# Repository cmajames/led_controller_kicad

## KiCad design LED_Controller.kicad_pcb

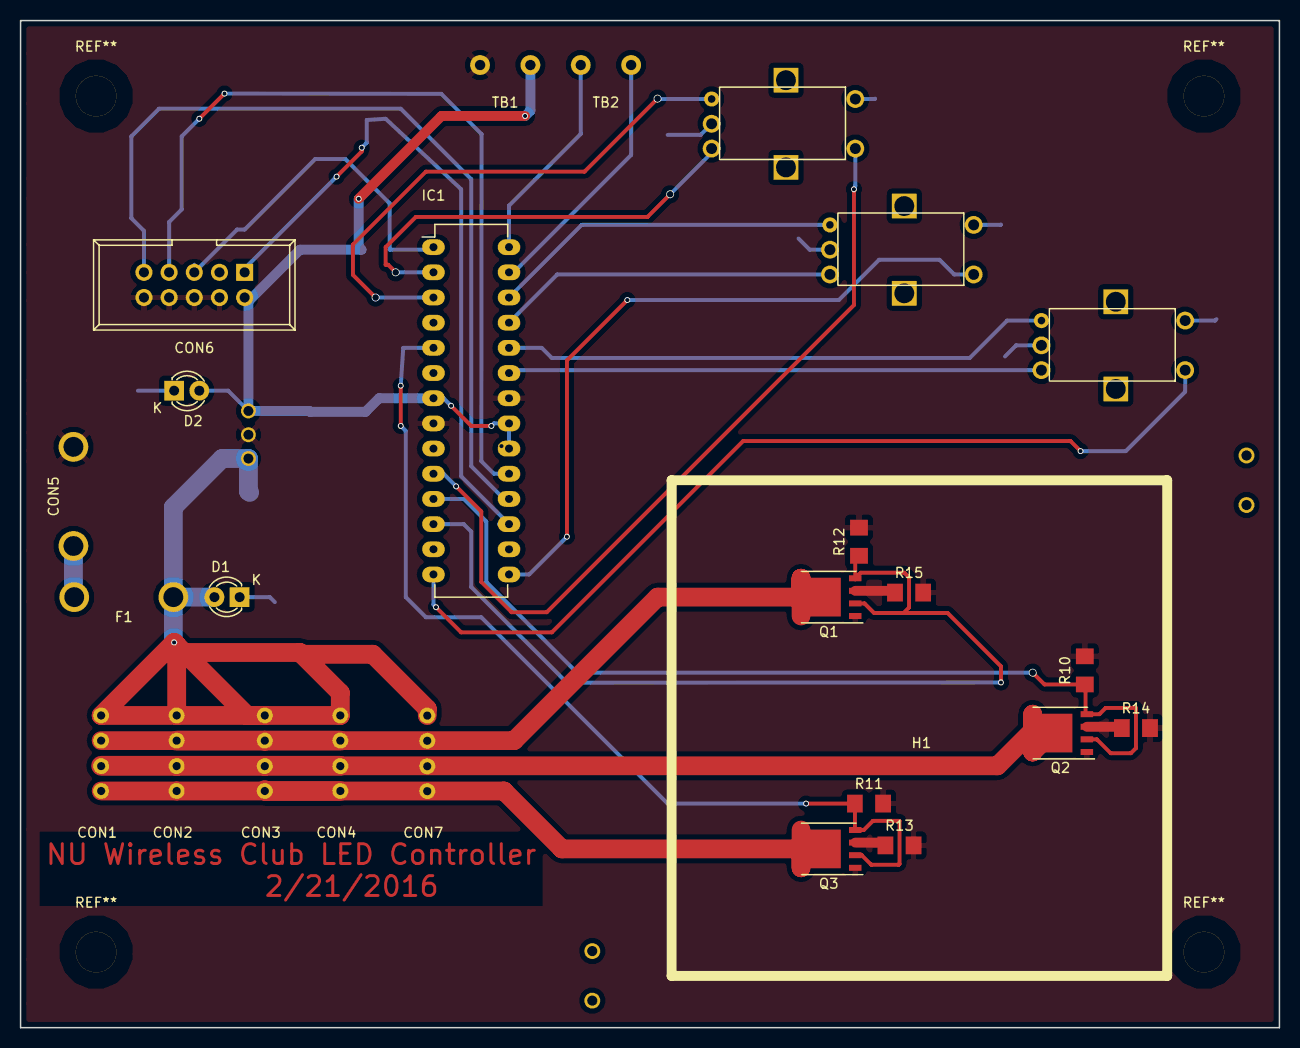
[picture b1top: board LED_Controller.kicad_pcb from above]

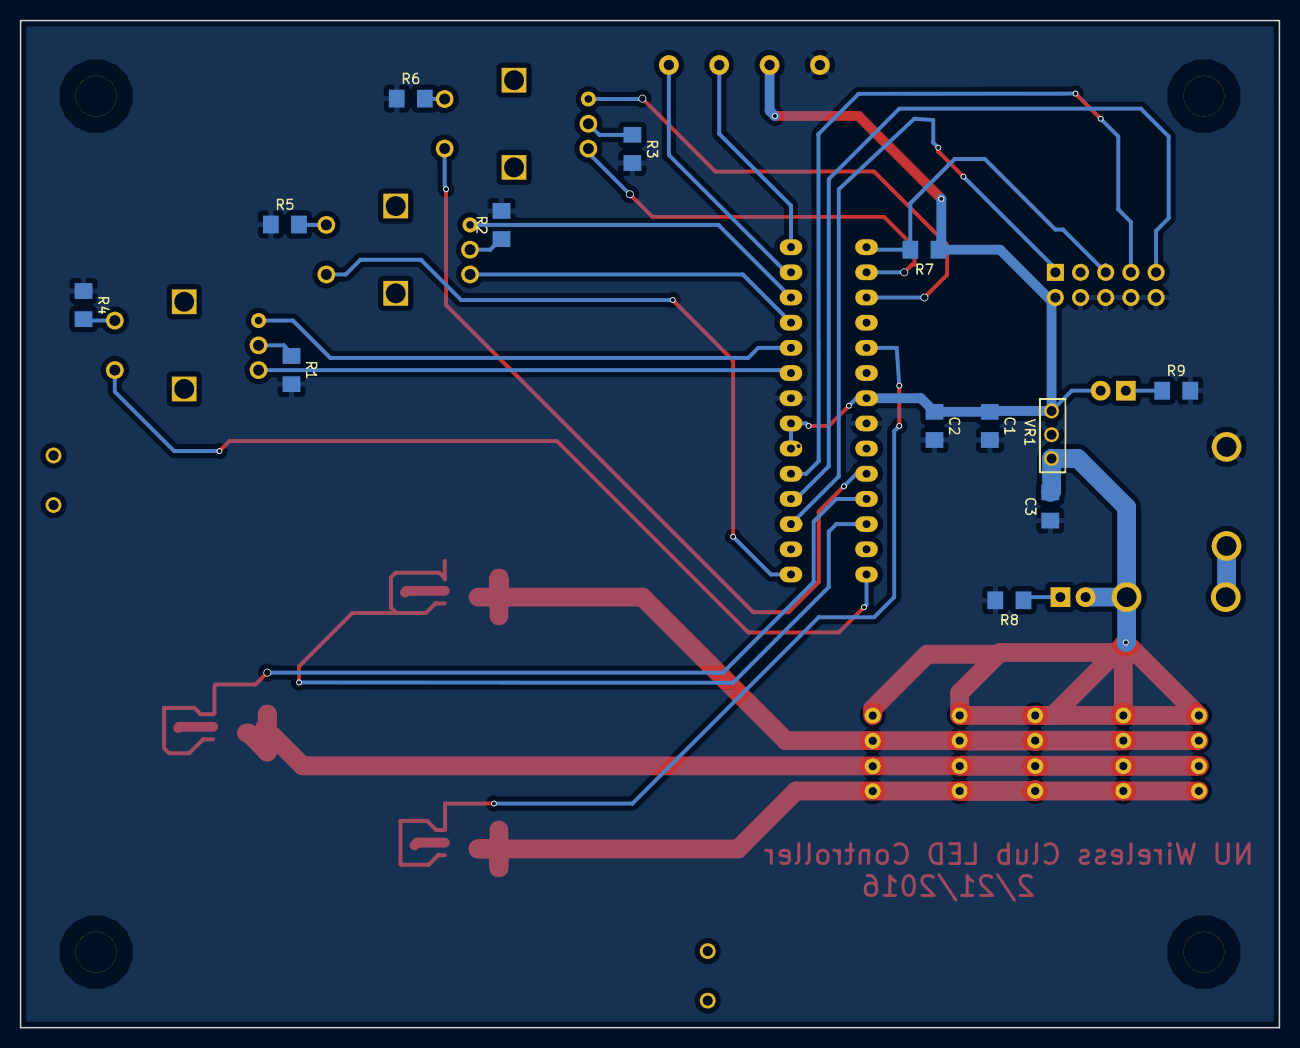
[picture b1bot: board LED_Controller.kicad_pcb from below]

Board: 2 copper layers, 127.0 x 101.6 mm, 39 parts (13 on the bottom side), 33 nets.

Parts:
C1, C3: 10uF; SMD_1206
C2: .1uF; SMD_1206
CON1, CON2, CON3, CON4, CON7: CONNECTOR; OUTPUT_HOLES
CON5: PWR_CON; 12V_PWR_HOLES
CON6: AVR-ISP-10; IDC_Header_Straight_10pins
D1, D2: LED; LED-3MM
E1, E2, E3: Rotary_Encoder; Rotary_encoder
F1: FUSE; 12V_PWR_HOLES
H1: Heatsink_50x50mm
IC1: ATMEGA328P-P; DIP-28_W7.62mm_LongPads
Q1, Q2, Q3: STS8DN3LLH5; SO-8_PowerPAK_Vishay_Single
R1, R2, R3, R4, R5, R6, R7, R10, R11, R12: 10k; SMD_1206
R8: 820; SMD_1206
R9: 499; SMD_1206
R13, R14, R15: 0; SMD_1206
TB1, TB2: Terminal_Block_2pin; Screw_Terminal
VR1: L7805CV

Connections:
+5V: C1.1, C2.1, CON6.2, D2.2, IC1.7, IC1.20, IC1.21, R7.1, TB1.1, VR1.3
+12V: C3.2, CON1.4, CON2.4, CON3.4, CON4.4, CON7.4, D1.2, F1.1, VR1.1
/BLUE_5V: IC1.12, Q1.2, Q1.4, R12.1
/BLUE_PWR: CON1.3, CON2.3, CON3.3, CON4.3, CON7.3, Q1.5
/GREEN_5V: IC1.11, Q2.2, Q2.4, R10.1
/GREEN_PWR: CON1.2, CON2.2, CON3.2, CON4.2, CON7.2, Q2.5
/MISO: CON6.9, IC1.18
/MOSI: CON6.1, IC1.17
/RED_5V: IC1.5, Q3.2, Q3.4, R11.1
/RED_PWR: CON1.1, CON2.1, CON3.1, CON4.1, CON7.1, Q3.5
/RST: CON6.5, IC1.1, R7.2
/SCK: CON6.7, IC1.19
/SCL: IC1.28, TB2.2
/SDA: IC1.27, TB2.1
GND: C1.2, C2.2, C3.1, CON5.2, CON6.4, CON6.6, CON6.8, CON6.10, IC1.8, IC1.22, Q1.1, Q1.3, Q2.1, Q2.3, Q3.1, Q3.3, R1.2, R2.2, R3.2, R4.1, R5.1, R6.1, R8.2, R9.2, R10.2, R11.2, R12.2, R13.1, R13.2, R14.1, R14.2, R15.1, R15.2, TB1.2, VR1.2
unnamed: CON5.1, F1.2
unnamed: D1.1, R8.1
unnamed: D2.1, R9.1
unnamed: E1.1, IC1.14
unnamed: E1.2, R4.2
unnamed: E1.3, R1.1
unnamed: E1.4, IC1.23
unnamed: E1.5, IC1.24
unnamed: E2.1, IC1.15
unnamed: E2.2, R5.2
unnamed: E2.3, R2.1
unnamed: E2.4, IC1.25
unnamed: E2.5, IC1.26
unnamed: E3.1, IC1.10
unnamed: E3.2, R6.2
unnamed: E3.3, R3.1
unnamed: E3.4, IC1.2
unnamed: E3.5, IC1.3

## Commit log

2016-02-14 Added kicad files
    Added schematic, PCB, and library files
2016-02-15 Minor Changes
    Added a pull-up resistor to RST, to ensure chip is not reset during
    normal use. Some minor changes to the track layout.
2016-02-19 Changed to Common Anode, new status LEDs
    Updated schematic to reflect common anode LED strip, instead of common
    cathode.
    Added indicator LEDs to 12V and 5V power supply.
    Other minor routing changes. Still need to update footprint to make
    rotary encoder pins larger and probably change the Atmega footprint to
    the correct size.
2016-02-20 Atmega footprint updated, SS Pin changed, Heatsink footprint added
    Atmega328p footprint now correct size
    Added SS pin for SPI
    Made and placed footprint for 50mm square heatsink
2016-02-20 Changed passive sizes, re-routed traces
    Changed all passive components to 1206 size (that size is stocked in
    the lab, and it should be easier to solder without a scope)
    Created a general 1206 footprint for resistors and capacitors
    Re-routed traces to MOSFETs and rotary encoders, tried to minimize
    number of vias
2016-02-21 Rewired FETs
    corrected incorrectly wired MOSFETs in schematic, updated traces
2016-02-22 Changed some encoder pins, wired outputs for I2C instead os SPI, generated gerber for milling
    Re-adjusted resistors to ensure proper milling
    Removed 6-pin header for SPI
    Added schematic and component for 2-terminal screw block
    Wired SCL and SDA to terminal block, added another terminal block for
    GND and +5V and routed traces
    Re-wired and traced pins for rotary encoder 3 to PD0 and PD1 (they were
2016-02-24 More output pins for LED strips, mounting holes added
    Updated size of LED output holes for LED strips
    Added more output footprints for strips
    Added mounting holes to corners of board; are probably incorrect size,
    modify later
    Exported updated gerbers
2016-02-24 Quick Fixes
    Connected unconnected trace to one of the LED strip holes
    Re-exported Gerber files
2016-03-04 Minor Changes
    Removed hidden unconnected via
    Re-exported gerbers and drill file
